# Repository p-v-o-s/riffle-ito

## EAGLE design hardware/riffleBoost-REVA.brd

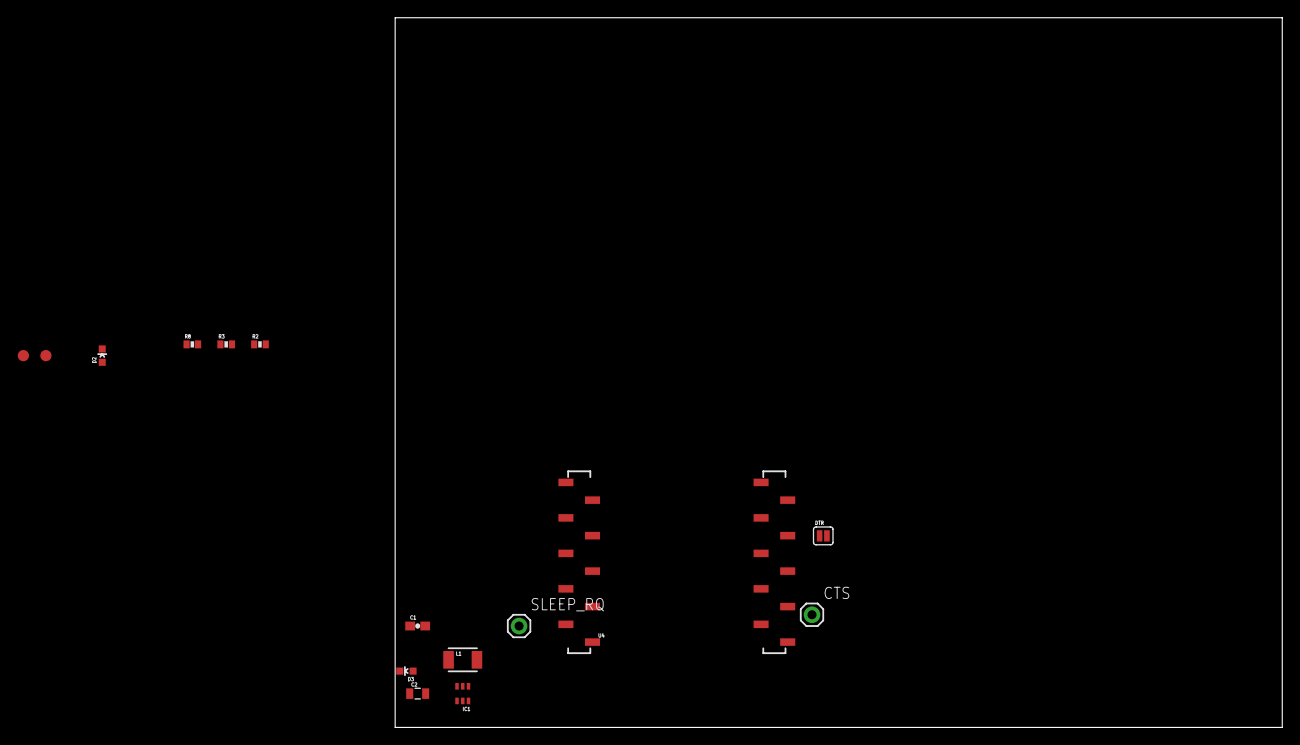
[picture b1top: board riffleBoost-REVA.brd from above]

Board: 2 copper layers, 100.0 x 80.0 mm, 15 parts (0 on the bottom side), 12 nets, no tracks yet.

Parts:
C1: 1µ; 0603-CAP
C2: 10µ; 0805
CTS: 1X01
D2: Green; LED-0603
D3: Red; LED-0603
DTR: SOLDERJUMPERNC; SJ_2S
IC1: LTC3525; SC70
L1: 10 µH; 1210
R2, R3: 1k; 0402-RES
R8: 100; 0402-RES
SLEEP_RQ: 1X01
TP1: RSSI; PAD.03X.05
TP2: ON; PAD.03X.05
U4: XBEE-1B3; XBEE-SMD

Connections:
CTS: CTS.1, U4.12
GND: C1.2, C2.2, D2.C, D3.C, IC1.2, IC1.5, U4.10
unnamed: C1.1, IC1.1, IC1.3, L1.1
unnamed: R2.2, TP1.P$1, U4.6
unnamed: D2.A, R2.1
unnamed: IC1.6, L1.2
unnamed: R3.2, TP2.P$1, U4.13
unnamed: D3.A, R3.1
unnamed: R8.2, U4.3
unnamed: DTR.1, U4.17
SLEEP_RQ: SLEEP_RQ.1, U4.9
VCC: C2.1, IC1.4, U4.1

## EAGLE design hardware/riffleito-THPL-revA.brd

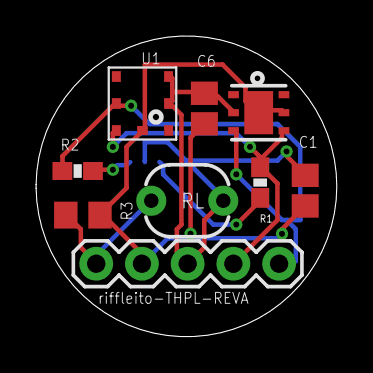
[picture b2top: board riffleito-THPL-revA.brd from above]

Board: 2 copper layers, 16.7 x 16.7 mm, 10 parts (1 on the bottom side), 7 nets.

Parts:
C1: 10u; C0805
C6: .1u; C0805
JP1: 1X05
R1, R2: 4.7K; 0603-RES
R3: 10K; R0805
RL: PHOTOCELL
SJ1: SJ_3_PASTE1&2&3
U1: BMP180
U2: SHT21; SEN-SENSIRION-SHT2X

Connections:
3.3V: C1.1, C6.1, JP1.3, RL.2, SJ1.2, U1.2, U1.3, U2.5
A0: JP1.5, R3.1, RL.1
GND: C1.2, C6.2, JP1.4, R3.2, U1.7, U2.2, U2.7
unnamed: R1.2, SJ1.3
unnamed: R2.2, SJ1.1
SCL: JP1.1, R2.1, U1.5, U2.6
SDA: JP1.2, R1.1, U1.6, U2.1

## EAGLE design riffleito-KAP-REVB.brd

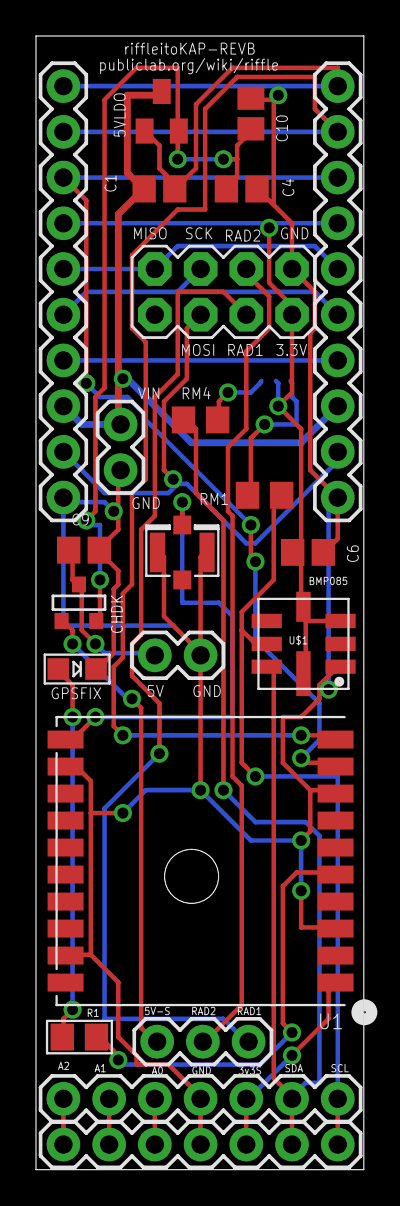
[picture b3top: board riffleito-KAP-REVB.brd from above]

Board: 2 copper layers, 18.2 x 63.0 mm, 23 parts (1 on the bottom side), 25 nets.

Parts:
5VLDO: MCP1700-5; SOT23
5VSWITCH: M02PTH; 1X02
BAT: M02PTH; 1X02
C1, C4: 10u; C0805
C6, C9, C10: .1u; C0805
CHDK: FDN340P; SOT-23
GPSFIX: FIX; CHIPLED_0805
I2CPULLUP: SJ_3_PASTE1&2&3
JP1: 1X03
JP3, JP5: M10"; 1X10
JP4, JP6: 1X07
R1: 1K; 0805
RAD: M04X2; 2X4
RM1: 10k; R0805
RM4: 10K; R0805
U1: FGPMMOPA6H
U$1: BMP085
U$20: U.FL

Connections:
3.3V: C6.1, I2CPULLUP.2, JP3.7, JP5.7, RAD.2, U$1.P$3, U$1.P$4, U$1.P$8
3V3SWITCH: JP4.3, JP6.3, U1.P$1
5V: 5VLDO.2, C4.1, C10.1, CHDK.2
5VOUT: 5VSWITCH.2, C9.2, CHDK.1
5VSWITCH: CHDK.3, JP1.1
A0: JP4.5, JP6.5
A1: JP4.6, JP6.6
A2: JP4.7, JP6.7
D6: JP3.8, JP5.8, U1.P$9
D8: JP3.9, JP5.9, U1.P$10
GND: 5VLDO.1, 5VSWITCH.1, BAT.1, C1.2, C4.2, C6.2, C9.1, C10.2, GPSFIX.C, JP3.1, JP3.10, JP4.4, JP5.1, JP5.10, JP6.4, RAD.1, U1.P$3, U1.P$8, U1.P$12, U1.P$19, U$1.P$1, U$20.P$1, U$20.P$2
MISO: JP3.6, JP5.6, RAD.7
MOSI: JP3.2, JP5.2, RAD.6
unnamed: GPSFIX.A, R1.1
unnamed: R1.2, U1.P$5
unnamed: I2CPULLUP.3, RM1.2
unnamed: U1.P$11, U$20.P$3
unnamed: I2CPULLUP.1, RM4.2
RADIO1: JP1.3, RAD.4
RADIO2: JP1.2, RAD.3
RESET: JP3.4, JP5.4
SCK: JP3.5, JP5.5, RAD.5
SCL: JP4.1, JP6.1, RM1.1, U$1.P$6
SDA: JP4.2, JP6.2, RM4.1, U$1.P$7
VIN: 5VLDO.3, BAT.2, C1.1, JP3.3, JP5.3

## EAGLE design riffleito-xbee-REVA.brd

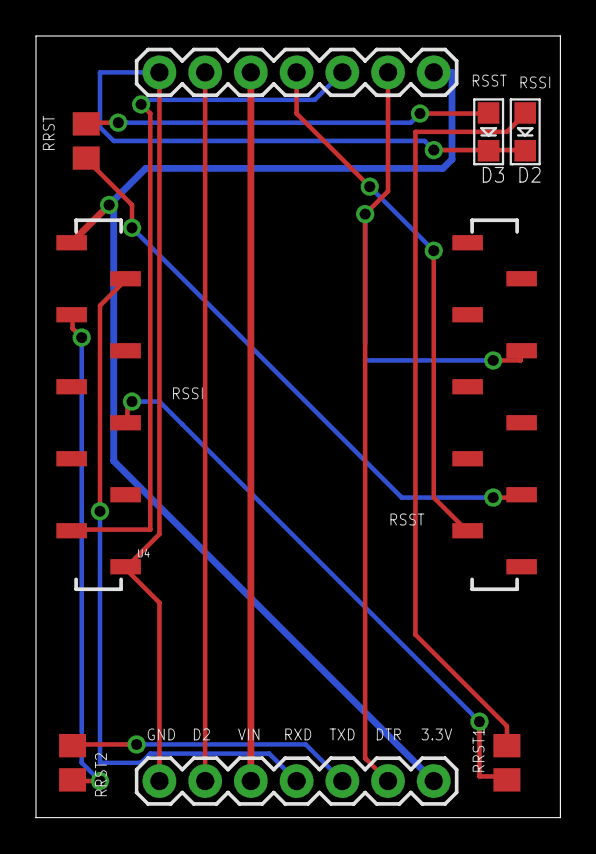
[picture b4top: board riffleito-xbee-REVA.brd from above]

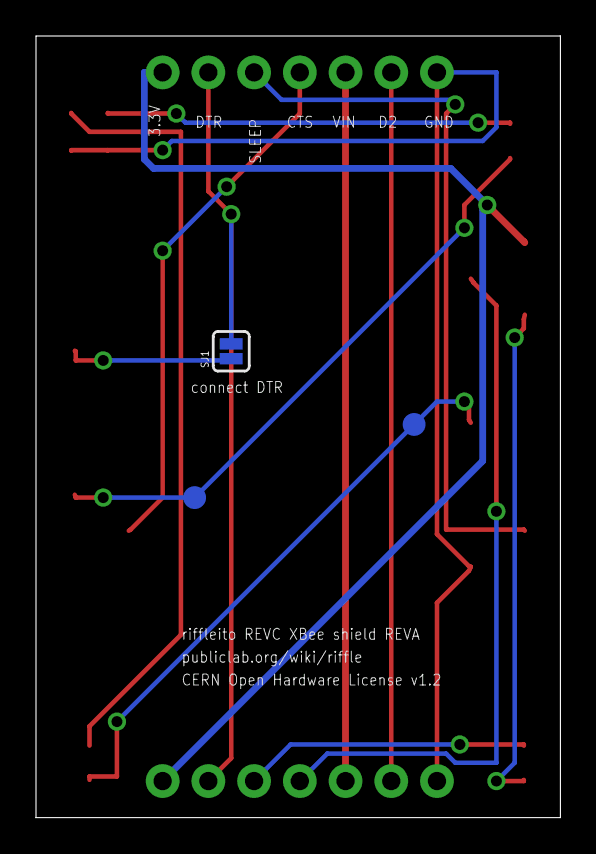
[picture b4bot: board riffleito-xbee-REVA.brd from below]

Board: 2 copper layers, 29.1 x 43.4 mm, 11 parts (3 on the bottom side), 15 nets.

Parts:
D2: GREEN; CHIPLED_0805
D3: RED; CHIPLED_0805
JP1, JP5: 1X07
RRST: 1K; R0805
RRST1, RRST2: 10K; R0805
SJ1: SOLDERJUMPERNC; SJ_2S
TP1: RSSI; PAD.03X.05
TP2: ON; PAD.03X.05
U4: XBEE-1B3; XBEE-SMD

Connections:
CTS: JP5.4, U4.12
D2: JP1.6, JP5.6
DTR: JP1.2, JP5.2, SJ1.2
GND: D2.C, D3.C, JP1.7, JP5.7, U4.10
unnamed: RRST.1, TP2.P$1, U4.13
unnamed: D2.A, RRST1.2
unnamed: RRST1.1, TP1.P$1, U4.6
unnamed: D3.A, RRST.2
unnamed: RRST2.2, U4.3
unnamed: SJ1.1, U4.17
RXD: JP1.4, U4.2
SLEEP_RQ: JP5.3, U4.9
TXD: JP1.3, RRST2.1
VCC: JP1.1, JP5.1, U4.1
VIN: JP1.5, JP5.5

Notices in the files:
hardware/riffleito-THPL-revA.brd:
CERN OHL v1.2
riffleito-xbee-REVA.brd:
CERN Open Hardware License v1.2
parts and their libraries:
SparkFun-Sensors: Licensing: CC v3.0 Share-Alike You are welcome to use this library for commercial purposes.
SparkFun-Connectors: Licensing: Creative Commons ShareAlike 4.0 International - https://creativecommons.org/licenses/by-sa/4.0
